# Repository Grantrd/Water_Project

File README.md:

# Water Quality Monitoring Project
This project for Dr. Gary Mahoney and Dr. Wei Wu, a collaboration between Scott Heggen, Wei Wu and Rodney Grant. It is meant to allow for the measuring and recording of the quality of water in lakes. The project consists of code written in the Arduino ide, using many of its common libraries. It utulizes Eagle Autocad Software for making the schematics and boards, and _________ to mill the PCB's. This is a school project funded by Berea College.

## Specifications
The board we are creating is made for an Arduino Pro Mini, and acts as a shield for it. Therefore the legs of the Pro will need to be soldered going up and have the board sit on top of the Arduino. The board is 1.04 inches across by 1.79 inches long. 

## Required Components
To use this project you will need: 
- An Arduino Pro Mini
- To be able to mill a PCB/ have the milled PCB 
- A 4.7K ohm resistor and a Digital Temperature probe
- An Arduino Micro SD adapter.  
- An analog light sensor
- A real time clock
- 2 1K to 500K Potentiometers
- A set of molex connectors
- A 6 Pin 90 degree Female header terminal.   

## Getting Started
To use the project you need to install the Arduino programming software. Open the code folder of the project, and copy the contents of the arduino libraries folder into the libraries folder of your arduino software, typically located in yourUserName\Documents\Arduino\libraries. Plug in your Arduino Mini Pro and open the Arduino Software. In the software go to "tools" -- "board" -- "Arduino Pro or Pro Mini". Then Go to open and select the Gary_Node_Temp.ino file located in the Arduino Code folder inside the Code folder of the Project. Then Go to "tools" -- "port" and select the port with the arduino connected, you can unplug and replug the arduino to see which port it connects to. Finally verify and upload the code onto the arduino. If the code will not verify, make sure the libraries are located in the correct folder.  

## The Board
Note if you already have the PCB, you can skip the milling section.  

### Milling the Board
...

### Soldering the board 
To solder the board you will need a soldering iron, solder, a milled PCB, and all of the required components listed above. 
You will need to solder the components for the board according to their location on the color coded diagram found under Board Layout. 

For the following components you will need to solder female ended molexes connectors to the board in place of the components, and solder male headed molex connectors to the ends of the components. They will then plug into each other.
- Temperature Probe
- Real Time Clock
- Power Switch
- Light Sensor

For the following components you will need to solder the components themselves to the board directly.
- Power Switch
- 4.7K Resistor
- 2 Potentiometers

For the Micro SD Writer you need to solder a 90 degree 6 pin female header terminal.

### Board Layout

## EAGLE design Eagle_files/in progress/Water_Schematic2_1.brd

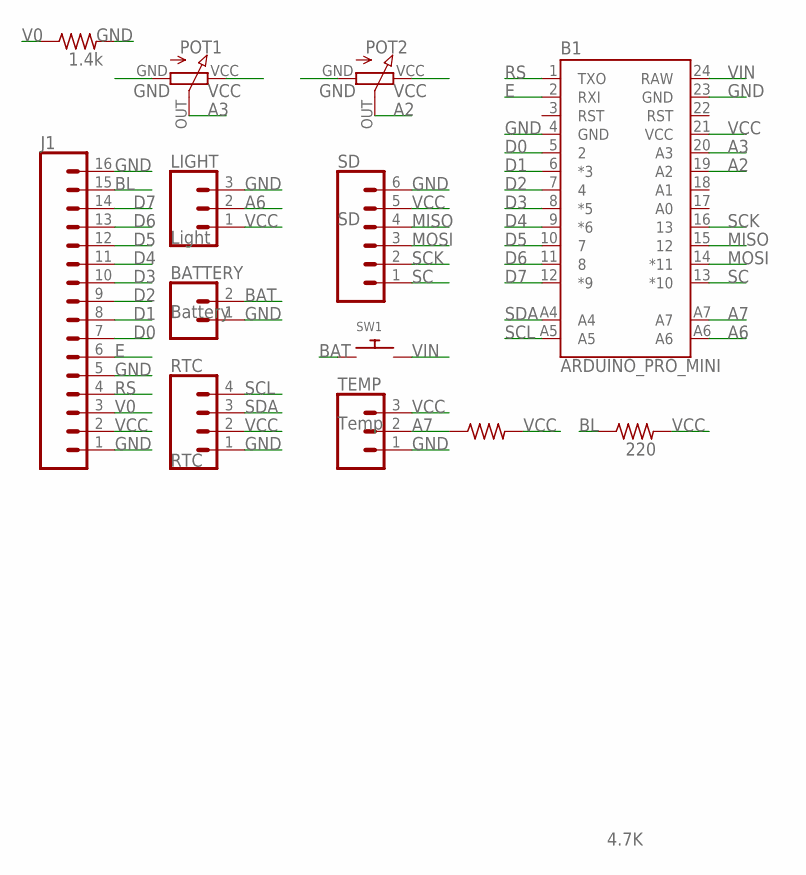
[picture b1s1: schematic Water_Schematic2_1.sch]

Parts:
B1: ARDUINO_PRO_MINI
BATTERY: Battery; MOLEX-1X2
J1: CONN_16; 1X16
LIGHT: Light; 1X03
POT1, POT2: RM_065
R1: 4.7K; 0204/7
R2: 220; 0204/7
R3: 1.4k; 0204/7
RTC: RTC; MOLEX-1X4
SD: SD; 1X06
SW1: SWITCH_PUSHBUTTONEVQ-PE; TACT_PANA-EVQ
TEMP: Temp; 1X03

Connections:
A2: B1.19 (A2), POT2.OUT
A3: B1.20 (A3), POT1.OUT
A6: B1.A6, LIGHT.2
A7: B1.A7, R1.1, TEMP.2
BAT: BATTERY.2, SW1.P$1
BL: J1.15, R2.1
D0: B1.5 (2), J1.7
D1: B1.6 (*3), J1.8
D2: B1.7 (4), J1.9
D3: B1.8 (*5), J1.10
D4: B1.9 (*6), J1.11
D5: B1.10 (7), J1.12
D6: B1.11 (8), J1.13
D7: B1.12 (*9), J1.14
E: B1.2 (RXI), J1.6
GND: B1.4 (GND), B1.23 (GND), BATTERY.1, J1.1, J1.5, J1.16, LIGHT.3, POT1.GND (GROUND), POT2.GND (GROUND), R3.2, RTC.1, SD.6, TEMP.1
MISO: B1.15 (12), SD.4
MOSI: B1.14 (*11), SD.3
RS: B1.1 (TXO), J1.4
SC: B1.13 (*10), SD.1
SCK: B1.16 (13), SD.2
SCL: B1.A5, RTC.4
SDA: B1.A4, RTC.3
V0: J1.3, R3.1
VCC: B1.21 (VCC), J1.2, LIGHT.1, POT1.VCC, POT2.VCC, R1.2, R2.2, RTC.2, SD.5, TEMP.3
VIN: B1.24 (RAW), SW1.P$2

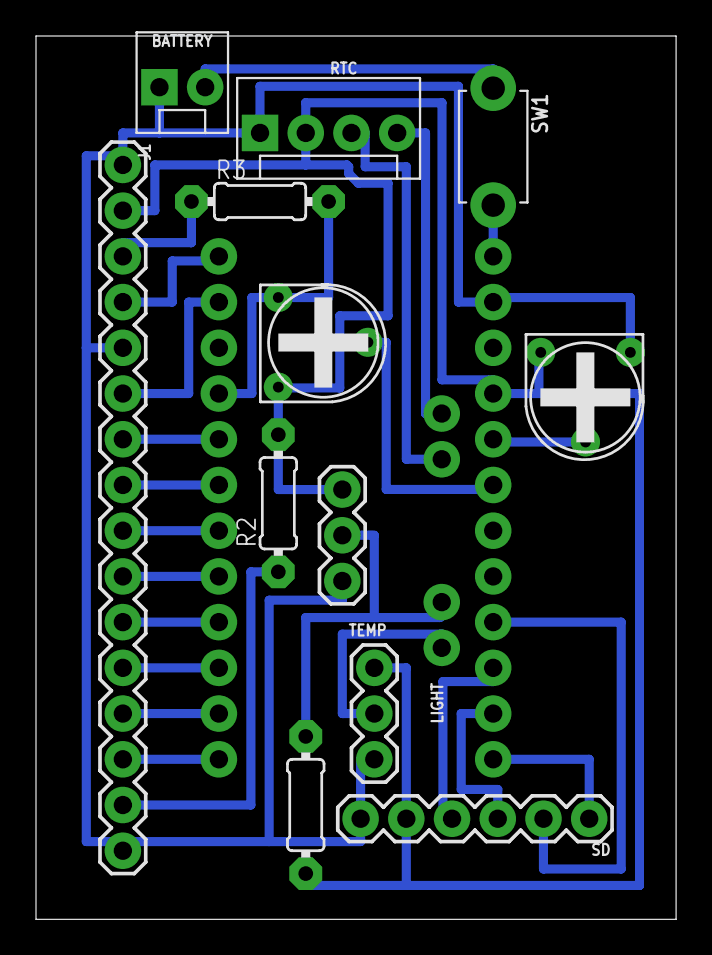
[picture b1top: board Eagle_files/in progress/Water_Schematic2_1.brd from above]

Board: 2 copper layers, 35.6 x 49.1 mm, 13 parts (0 on the bottom side), 26 nets.

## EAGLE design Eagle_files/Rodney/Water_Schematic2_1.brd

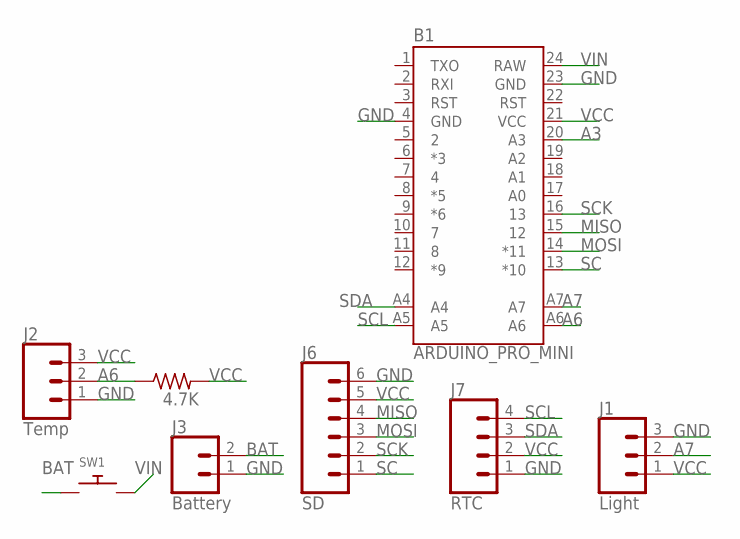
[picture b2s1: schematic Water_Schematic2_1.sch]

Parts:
B1: ARDUINO_PRO_MINI
J1: Light; 1X03
J2: Temp; 1X03
J3: Battery; MOLEX-1X2
J6: SD; 1X06
J7: RTC; MOLEX-1X4
R1: 4.7K; 0204/7
SW1: SWITCH_PUSHBUTTONEVQ-PE; TACT_PANA-EVQ

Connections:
A3: B1.20 (A3)
A6: B1.A6, J2.2, R1.1
A7: B1.A7, J1.2
BAT: J3.2, SW1.P$1
GND: B1.4 (GND), B1.23 (GND), J1.3, J2.1, J3.1, J6.6, J7.1
MISO: B1.15 (12), J6.4
MOSI: B1.14 (*11), J6.3
SC: B1.13 (*10), J6.1
SCK: B1.16 (13), J6.2
SCL: B1.A5, J7.4
SDA: B1.A4, J7.3
VCC: B1.21 (VCC), J1.1, J2.3, J6.5, J7.2, R1.2
VIN: B1.24 (RAW), SW1.P$2

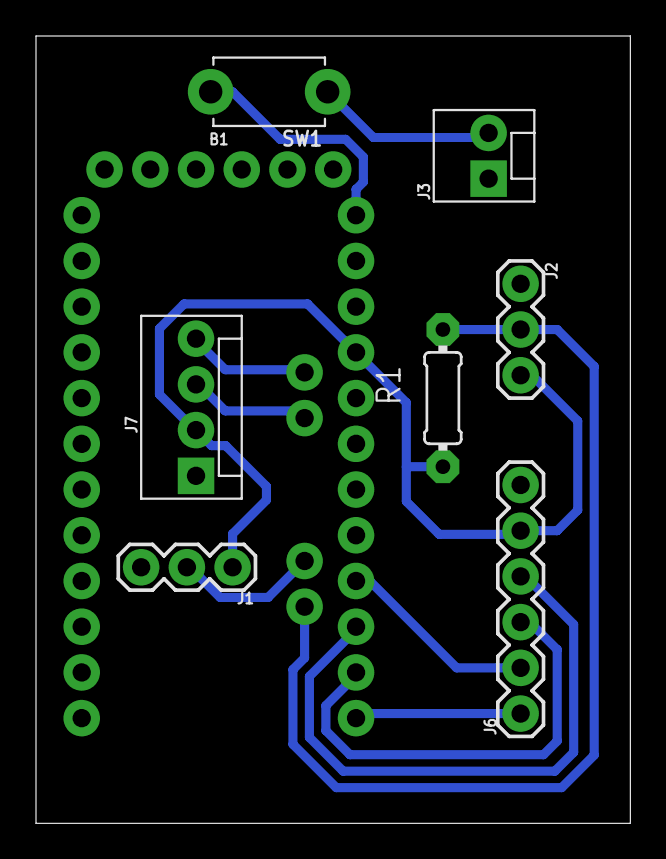
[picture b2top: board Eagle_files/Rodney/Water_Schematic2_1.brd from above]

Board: 2 copper layers, 33.0 x 43.7 mm, 8 parts (0 on the bottom side), 12 nets.

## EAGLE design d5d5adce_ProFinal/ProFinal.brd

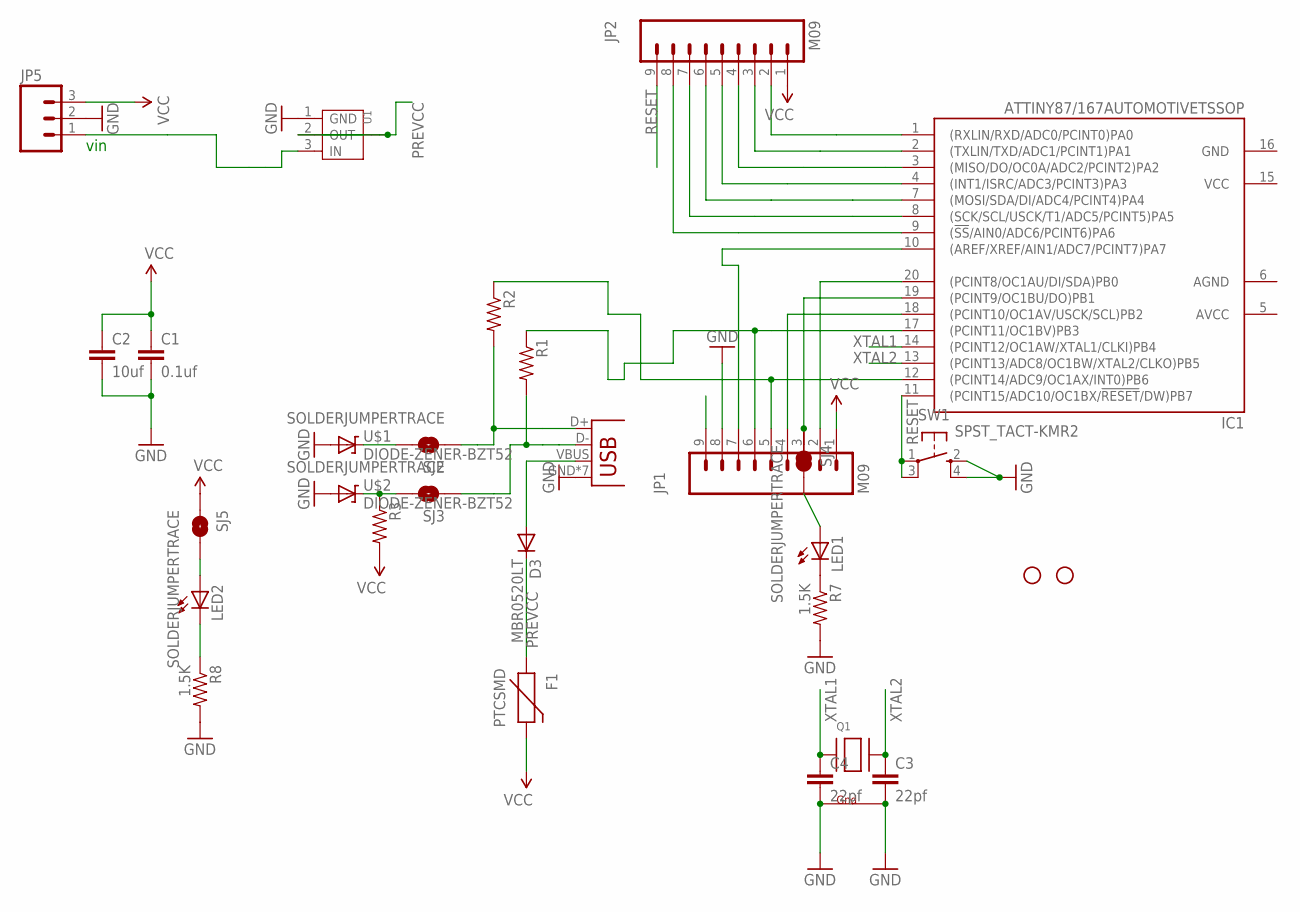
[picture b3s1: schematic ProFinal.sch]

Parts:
C1: 0.1uf; 0603-CAP
C2: 10uf; 0805
C3, C4: 22pf; 0603-CAP
D3: MBR0520LT; SOD123
F1: PTCSMD; PTC-1206
IC1: ATTINY87/167AUTOMOTIVETSSOP; TSSOP20
JP1, JP2: M09; 1X09
JP5: M03PTH; 1X03
LED1, LED2: LEDCHIP-LED0805; CHIP-LED0805
Q1: XTAL-4-3225; NX3225
R1, R2, R3: RESISTOR0603-RES; 0603-RES
R7, R8: 1.5K; 0603-RES
SJ2, SJ3, SJ4, SJ5: SOLDERJUMPERTRACE; SJ_2S-TRACE
STANDOFF3, STANDOFF4: STAND-OFFTIGHT; STAND-OFF-TIGHT
SW1: SPST_TACT-KMR2; KMR2
U1: LD1117SOT89; SOT89
U$1, U$2: DIODE-ZENER-BZT52; SOD-323
X1: USB-MICROB

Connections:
GND: C1.2, C2.2, C3.2, C4.2, IC1.16 (GND), JP1.8, JP5.2, Q1.2 (G2), Q1.4 (G1), R7.2, R8.2, SW1.2 (S), SW1.4 (S1), U1.1 (GND), U$1.2 (A), U$2.2 (A), X1.GND, X1.P1 (GND), X1.P2 (GND), X1.P3 (GND), X1.P4 (GND), X1.P5 (GND), X1.P6 (GND)
unnamed: IC1.20 ((PCINT8/OC1AU/DI/SDA)PB0), JP1.2
unnamed: IC1.12 ((PCINT14/ADC9/OC1AX/INT0)PB6), JP1.5, R2.1
unnamed: IC1.19 ((PCINT9/OC1BU/DO)PB1), JP1.3, SJ4.1
unnamed: IC1.1 ((RXLIN/RXD/ADC0/PCINT0)PA0), JP2.2
unnamed: IC1.2 ((TXLIN/TXD/ADC1/PCINT1)PA1), JP2.3
unnamed: IC1.3 ((MISO/DO/OC0A/ADC2/PCINT2)PA2), JP2.4
unnamed: IC1.4 ((INT1/ISRC/ADC3/PCINT3)PA3), JP2.5
unnamed: IC1.7 ((MOSI/SDA/DI/ADC4/PCINT4)PA4), JP2.6
unnamed: IC1.18 ((PCINT10/OC1AV/USCK/SCL)PB2), JP1.4
unnamed: R1.2, SJ3.1, X1.D-
unnamed: R2.2, SJ2.1, X1.D+
unnamed: IC1.8 ((SCK/SCL/USCK/T1/ADC5/PCINT5)PA5), JP2.7
unnamed: IC1.9 ((!SS!/AIN0/ADC6/PCINT6)PA6), JP2.8
unnamed: IC1.10 ((AREF/XREF/AIN1/ADC7/PCINT7)PA7), JP1.7
unnamed: IC1.17 ((PCINT11/OC1BV)PB3), JP1.6, R1.1
unnamed: SJ2.2, U$1.1 (C)
unnamed: R3.1, SJ3.2, U$2.1 (C)
unnamed: LED1.C, R7.1
unnamed: LED1.A, SJ4.2
unnamed: LED2.A, SJ5.2
unnamed: LED2.C, R8.1
unnamed: D3.A, X1.VBUS
PREVCC: D3.C, F1.1, U1.2 (OUT), U1.4 (TAB)
RESET: IC1.11 ((PCINT15/ADC10/OC1BX/!RESET!/DW)PB7), JP2.9, SW1.1, SW1.3 (P1)
VCC: C1.1, C2.1, F1.2, IC1.15 (VCC), JP1.1, JP2.1, JP5.3, R3.2, SJ5.1
VIN: JP1.9, JP5.1, U1.3 (IN)
XTAL1: C4.1, IC1.14 ((PCINT12/OC1AW/XTAL1/CLKI)PB4), Q1.1 (X1)
XTAL2: C3.1, IC1.13 ((PCINT13/ADC8/OC1BW/XTAL2/CLKO)PB5), Q1.3 (X2)

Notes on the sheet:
vin

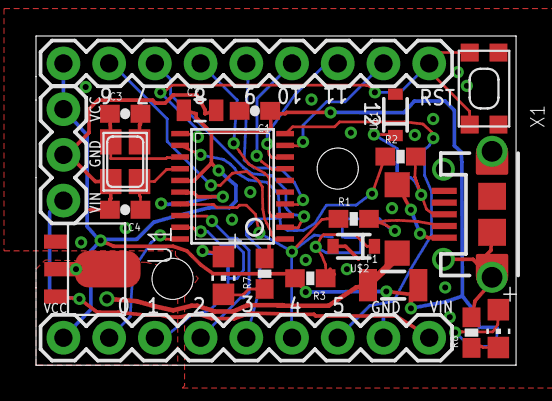
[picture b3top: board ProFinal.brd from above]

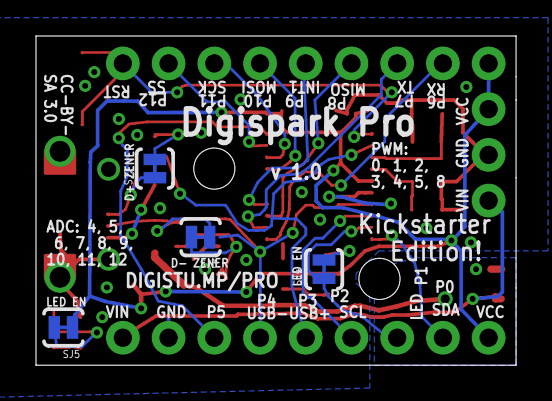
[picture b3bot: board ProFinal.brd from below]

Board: 2 copper layers, 26.7 x 18.3 mm, 29 parts (4 on the bottom side), 29 nets.

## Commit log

2019-11-08 initializing repo
2019-11-14 cam output for mill
2019-11-22 up to date
2019-12-12 New Arduino code that works with Scott's protoboard
2019-12-12 Moving files around to make things more clear
2019-12-12 Eagle files updated
2019-12-13 Updated code to remove any extra processing, such as Serial prints; Wakes up for sensing every 15m now also
2019-12-13 Minor tweaks to the board layout
2020-01-16 Added Arduino libraries needed for the code to work.
2020-01-24 added a more spaced out brd
2020-01-27 Updating board
2020-02-10 Updated design
2020-02-12 Title and tentative description
2020-02-14 updating readme
2020-02-14 trying to add image
2020-02-14 Trying image again
2020-02-14 added a getting started.
2020-02-14 got more of the readme done.
2020-02-17 Made Progress on the readme
2020-02-17 Made fixes to the readme
2020-02-18 Removing unnecessary files; minor tweaks to board and schematic, like removing value from pots
2020-02-19 working on screen
2020-02-24 almost there brd
2020-02-25 almost there!!!!!!
2020-02-25 got the latest schematic working
2020-02-26 attempt 2 lcd
2020-02-27 Removing unnecessary files, again. Made very minor change to board:
2020-02-27 Actually removed unnecessary files
2020-02-27 More unnecessary files removed

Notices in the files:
d5d5adce_ProFinal/ProFinal.brd:
CC-BY-
parts and their libraries:
SparkFun-Boards: Licensing: Creative Commons ShareAlike 4.0 International - https://creativecommons.org/licenses/by-sa/4.0
SparkFun: Licensing: CC v3.0 Share-Alike You are welcome to use this library for commercial purposes.
